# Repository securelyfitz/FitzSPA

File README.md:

FitzSPA
=======

Joe Fitz's Simple Power Analysis Tool

This is a simple board for monitoring power analysis of small microcontroller circuits.

See the slides from BsidesPDX here: http://goo.gl/m2waMq

## Changes
The major change in 1.1 is that there is now a 2nd potentiometer tied to the offset input of the amplifier. This allows you to dial in an offset so you can adjust to a larger differential gain without exceeding the input range of the A/D converter.

I thought i could get away without this in rev 1.0 but it has shown to be too important. Time will tell if a potentiometer is sufficient or i should have used a low impedance reference (at additional complexity, BOM cost, board space, and redesign time)

## Theory

The current across the shunt resistor Rv is measured with a differential amplifier U2. The output is digitized by the A-D converter, U1, which is triggered and synchronized by the device's own clock signal. The JP1 pins connect to a logic analyzer for sampling.

The differential amplifier will cancel out all sorts of common mode noise and only amplify the voltage across the Rv shunt resistor, which will be proportional to the instantaneous current draw of your target device. By synchronizing the A/D sampling to the device clock, we can get a digital readout at roughly the same time every clock cycle and not have to oversample 10x or more. Right now the Logic analyzer connection is asynchronous, but that should be fixed in future revisions.

Future versions will integrate a Cypress EZ-usb FX2 logic analyzer and power regulation, but they were excluded to reduce time and complexity for revision 1.x

##Using

Connect the logic analyzer to the J1 connector. Pin1 in the upper left is AD0, the LSB. The bottom two pins are both ground. If you have an 8-bit logic analyzer, start with the 8 MSBs, and if all of your sampling is in the same range, try connecting to less significant pins for higher gain.

Power +5vdc can come from a USB cable, an external supply, your logic analyzer, or from your target system

JP3 has a number of pins for various ways of connecting your shunt resistor and powering your target. Pins in order: VCC  Rv+  Rv-  GND  GND  CLK

To measure with a shunt on VCC, power supplied by FitzSPA:
* Connect VCC and Rv+ with a jumper
* Connect RV- to your target board's VCC
* Connect GND to your target board's GND
* Connect CLK to your target board's CLK

To measure with a shunt on GND, power supplied by FitzSPA:
* Connect VCC to your target board's VCC
* Connect Rv+ to your target board's ground
* Connect RV- and GND with a jumper
* Connect CLK to your target board's CLK

To measure with a shunt on VCC, with a separate external supply:
* Connect Rv+ to the external supply
* Connect RV- to your target board's VCC
* Connect GND to your target board's GND and external supply GND
* Connect CLK to your target board's CLK

To measure with a shunt on GND, power supplied by FitzSPA:
* Connect your external supply to the target board's VCC
* Connect Rv+ to your target board's ground
* Connect RV- and GND with a jumper
* Connect the second GND pin to the external supply's GND
* Connect CLK to your target board's CLK

Fire up your logic analyzer, turn on your board, and you should see the live power consumption updated each clock cycle!

##Building
Rev 1.1 is functional and continues to iron out some kinks. There are a few options for building out your board:

#### Differential Amplifier:
The AD8129 should provide much higher gains for more sensitive readings. However, I still haven't debugged why the AD8130 works fine and the AD8129 does not at G=10. For the time being, use the x30 unless you want to help the debug effort. the x29 is digikey AD8129ARMZ-ND
#### Gain setting circuit:
The gain of the differential amplifier is 1+(Rf/Rg). The default BOM uses 1k Ohm/100 Ohm, but you can vary this, or replace Rf with a potentiometer, such as digikey 987-1155-ND
####Voltage Regulator Load:
the 5v to +-12v regulator needs a minimum load to work properly. I haven't needed them, but populating R1 and R2 with 2.4k ohm resistors should provide the required load. digikey RMCF0603FT2K40CT-ND

####For the basic build you probably want:

Component | Description | Value | notes | Digikey | Price
--- | --- | --- | --- | --- | ---
U1 | AD9200ARZ | 20msps 10-bit A/D converter | | AD9200ARSZ-ND | 5.83
U2 | AD8130ARMZ | differential amplifier | AD8129 - unresolved issues. use AD8130 for now | AD8130ARMZ-ND | 4.06
U3 | VAT1-S5-D12-SMT | 5v to +-12v converter | | 102-1386-1-ND | 5.51
JP1 | 2x6 .1" header | | connects to LA | S1012EC-40-ND	| 0.51
JP2 | 1x3 .1" header | | connects ot power/ground | same as jp1 |
JP3 | 1x6 .1" header | | connects ot DUT | same as jp1 |
C1,C2,C3,C4,C5,C6,C7,C8 | 0603 SMT Capacitor | .1uF | | 587-1240-1-ND	| 0.10
C11,C12,C13,C14,C15,C16 | 0805 SMT Capacitor | 10uF | doesn't need to be electrolytic | 587-1295-1-ND | 0.25
R1,R2 | 0603 SMT resistor |  | leave empty unless needed to stabilize +-12v output |
R3 | 0603 SMT resistor | 150 ohm | LED series resistor | RMCF0603FT150RCT-ND | 0.04
R4 | 0603 SMT resistor | 10 ohm | provides a little isolation between digital and analog VCC | RMCF0603FT10R0CT-ND | 0.04
Rv | 0603 SMT resistor | 1 ohm | shunt resistor - DUT power crosses over this | RMCF0603FT1R00CT-ND	| 0.04 
Rg | 0603 SMT resistor | 100 ohm | gain resistor | RMCF0603FT100RCT-ND | 0.04
Rf1 | 0603 SMT resistor | 1k ohm | gain resistor | RMCF0603FT1K00CT-ND | 0.04
Rf | 84WR SMT Potentiometer |  | leave empty if using fixed Rf1 instead |
Rf2 | 84WR SMT Potentiometer |  | potentiometer for adjusting offset bluewire pin 4 to ground if you really don't want this |
LED | 0603 SMT LED | | | 475-2558-1-ND	| 0.09

The Digikey BOM is saved in FitzSPA-BOM.csv, you can upload or paste it's contents into the BOM wizard: https://www.digikey.com/classic/registereduser/BOMWizard.aspx

$18.50 + shipping

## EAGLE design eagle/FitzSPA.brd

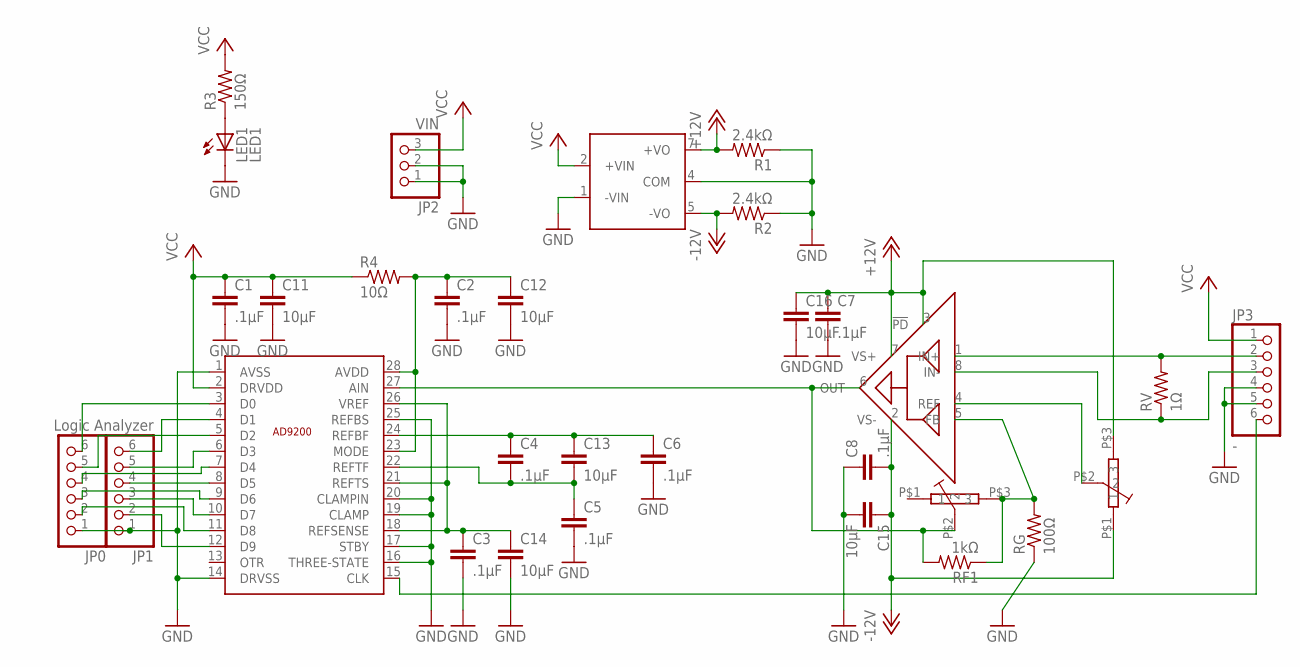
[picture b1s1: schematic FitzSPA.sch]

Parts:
C1, C2, C3, C4, C5, C6, C7, C8: .1µF; C0603
C11, C12, C13, C14, C15, C16: 10µF; C0805
JP0: 1X06-BIGLOCK
JP1: Logic Analyzer; 1X06-BIGLOCK
JP2: VIN; 1X03
JP3: -; 1X06-BIGLOCK
LED1: LED1; CHIPLED_0603
R1, R2: 2.4kΩ; R0603
R3: 150Ω; R0603
R4: 10Ω; R0603
RF, RF2: 10kΩ; MODEL84POT
RF1: 1kΩ; R0603
RG: 100Ω; R0603
RV: 1Ω; R0603
U1: AD9200ARZ; SSOP28
U2: AD8129ARMZ; MSOP8
U3: VAT1-SMT

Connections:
+12V: C7.1, C16.1, R1.2, RF2.P$3 (3), U2.3 (!PD), U2.7 (VS+), U3.7 (+VO)
-12V: C8.2, C15.1, R2.2, RF2.P$1 (1), U2.2 (VS-), U3.5 (-VO)
GND: C1.2, C2.2, C3.2, C5.2, C6.2, C7.2, C8.1, C11.2, C12.2, C14.2, C15.2, C16.2, JP0.1, JP1.1, JP2.1, JP2.2, JP3.4, JP3.5, LED1.C, R1.1, R2.1, RG.1, U1.1 (AVSS), U1.14 (DRVSS), U1.16 (THREE-STATE), U1.17 (STBY), U1.19 (CLAMP), U1.20 (CLAMPIN), U1.25 (REFBS), U3.1 (-VIN), U3.4 (COM)
unnamed: RF.P$2 (2), RF1.2, U1.27 (AIN), U2.6 (OUT)
unnamed: JP1.6, U1.4 (D1)
unnamed: RF.P$3 (3), RF1.1, RG.2, U2.5 (FB)
unnamed: C4.1, C6.1, C13.1, U1.24 (REFBF)
unnamed: JP1.5, U1.6 (D3)
unnamed: JP3.3, RV.1, U2.8 (IN-)
unnamed: C4.2, C5.1, C13.2, U1.22 (REFTF)
unnamed: C3.1, C14.1, U1.18 (REFSENSE), U1.21 (REFTS), U1.26 (VREF)
unnamed: JP1.4, U1.8 (D5)
unnamed: JP1.3, U1.10 (D7)
unnamed: JP1.2, U1.12 (D9)
unnamed: JP0.6, U1.3 (D0)
unnamed: JP0.5, U1.5 (D2)
unnamed: JP0.4, U1.7 (D4)
unnamed: JP0.3, U1.9 (D6)
unnamed: JP0.2, U1.11 (D8)
unnamed: LED1.A, R3.1
unnamed: JP3.2, RV.2, U2.1 (IN+)
unnamed: JP3.6, U1.15 (CLK)
unnamed: C2.1, C12.1, R4.2, U1.23 (MODE), U1.28 (AVDD)
unnamed: RF2.P$2 (2), U2.4 (REF)
VCC: C1.1, C11.1, JP2.3, JP3.1, R3.2, R4.1, U1.2 (DRVDD), U3.2 (+VIN)

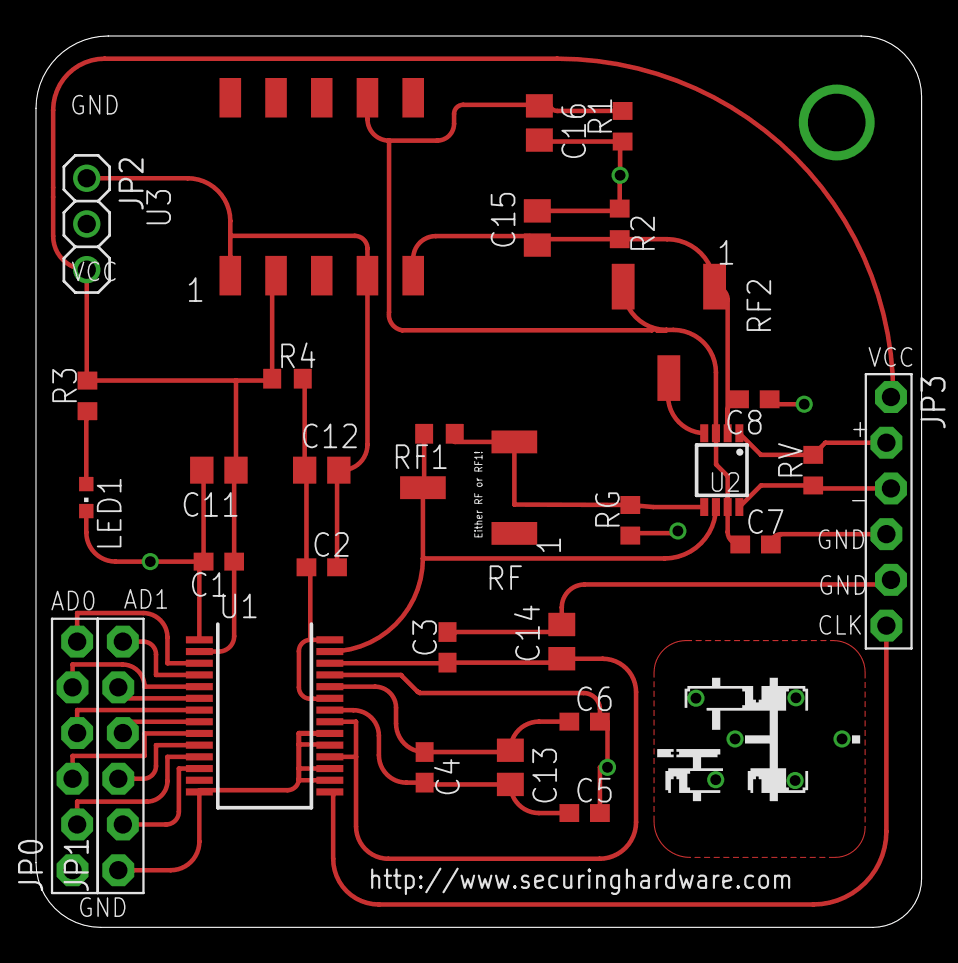
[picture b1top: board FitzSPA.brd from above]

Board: 2 copper layers, 49.2 x 49.5 mm, 33 parts (1 on the bottom side), 25 nets.

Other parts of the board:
U$4: SH-HALFINCH
U$5: SECURINGHARDWAREDOTCOM

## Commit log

2013-09-23 Update README.md
    added BOM parts in a table
2013-09-23 Update README.md
    Fill in parts, BOM detail, basic documentation and wiring instructions
2013-09-23 Added eagle, libraries, gerbers
2013-09-26 update 10uF caps to 0805 parts
2013-11-27 Moving to branches for revisions instead of file names
    changed filename
    added 2nd POT on pin 4 of the diff amp to give a variable offset
2013-11-27 script to convert bmp to eagle layers
2013-11-27 Fixing filenames, new revision
    shortened filenames
    removed version number from filename
    gerbers for version 1.1
2013-11-27 documenting changes for v1.1
2013-12-13 initial version for FitzSPA 1.0
2013-12-13 added potentiometers for version 1.1
